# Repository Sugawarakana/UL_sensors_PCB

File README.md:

## Note: This project has been migrated into ULDSG

## Project Overview
Eagle-based PCB design for the UL project at the University of Michigan, Ann Arbor — Battery Control Group.

## Files
- `Connection.brd` — PCB layout file
- `Connection.sch` — Schematic file

## Tools
- Autodesk Eagle 9.6.2

## Descriptions
- **JP1 & JP2:** Female pin headers for Nucleo G431KB

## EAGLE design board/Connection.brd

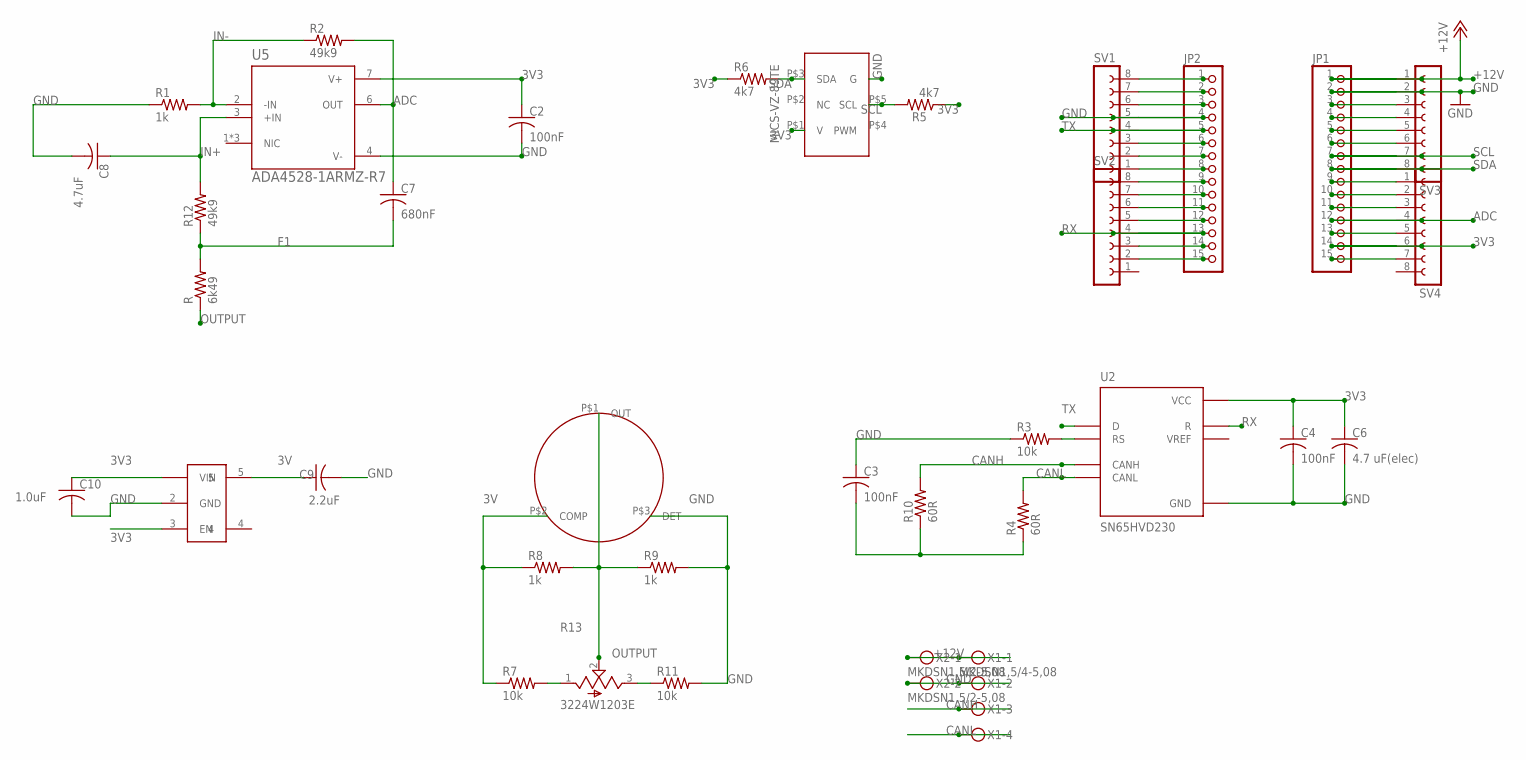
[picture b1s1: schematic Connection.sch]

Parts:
C2, C3, C4: 100nF; C0402
C6: 4.7 uF(elec); C0603
C7: 680nF; C1206
C8: 4.7uF; C1206
C9: 2.2uF; C0603
C10: 1.0uF; C0805
JP1, JP2: PINHD-1X15; 1X15
R: 6k49; R0603
R1, R8, R9: 1k; R0805
R2, R12: 49k9; R0603
R3, R7, R11: 10k; M1206
R4, R10: 60R; R0603
R5, R6: 4k7; M1206
R13: 3224W1203E; TRIM_3224W1203E
SV1, SV2, SV3, SV4: FE08-1; FE08
U2: SN65HVD230; SOIC127P599X175-8N
U5: ADA4528-1ARMZ-R7; SOP65P490X110-8N
U$1: MP7227; MP7227_FP
U$3: MIC5233
U$4: MICS-VZ-89TE; MICS-VZ-89TE_FP
X1: MKDSN1,5/4-5,08
X2: MKDSN1,5/2-5,08

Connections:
3V: C9.1, R7.1, R8.1, U$1.P$2 (COMP), U$3.5
3V3: C2.1, C4.1, C6.1, C10.1, JP1.14, R5.1, R6.1, SV4.6, U2.3 (VCC), U5.7 (V+), U$3.1 (VIN), U$3.3 (EN), U$4.P$1 (V); also elsewhere on the board
+12V: JP1.1, SV3.1, X1.1, X2.1; also elsewhere on the board
ADC: C7.1, JP1.12, R2.2, SV4.4, U5.6 (OUT); also elsewhere on the board
C1: C3.2, R4.1, R10.1
CANH: R10.2, U2.7 (CANH), X1.3
CANL: R4.2, U2.6 (CANL), X1.4
F1: C7.2, R.2, R12.1
GND: C2.2, C3.1, C4.2, C6.2, C8.2, C9.2, C10.2, JP1.2, JP2.4, R1.1, R3.1, R9.2, R11.2, SV1.5, SV3.2, U2.2 (GND), U5.4 (V-), U$1.P$3 (DET), U$3.2 (GND), U$4.P$6 (G), X1.2, X2.2; also elsewhere on the board
IN+: C8.1, R12.2, U5.3 (+IN)
IN-: R1.2, R2.1, U5.2 (-IN)
unnamed 12: JP1.6, SV3.6; also elsewhere on the board
unnamed 13: JP1.3, SV3.3; also elsewhere on the board
unnamed 14: JP1.4, SV3.4; also elsewhere on the board
unnamed 15: JP1.5, SV3.5; also elsewhere on the board
unnamed 16: JP1.9, SV4.1; also elsewhere on the board
unnamed 17: JP1.10, SV4.2; also elsewhere on the board
unnamed 18: JP1.11, SV4.3; also elsewhere on the board
unnamed 19: JP1.13, SV4.5; also elsewhere on the board
unnamed 20: JP1.15, SV4.7; also elsewhere on the board
unnamed 21: JP2.8, SV1.1; also elsewhere on the board
unnamed 22: JP2.7, SV1.2; also elsewhere on the board
unnamed 23: JP2.6, SV1.3; also elsewhere on the board
unnamed 24: JP2.3, SV1.6; also elsewhere on the board
unnamed 25: JP2.2, SV1.7; also elsewhere on the board
unnamed 26: JP2.1, SV1.8; also elsewhere on the board
unnamed 27: JP2.15, SV2.2; also elsewhere on the board
unnamed 28: JP2.14, SV2.3; also elsewhere on the board
unnamed 29: JP2.12, SV2.5; also elsewhere on the board
unnamed 30: JP2.11, SV2.6; also elsewhere on the board
unnamed 31: JP2.10, SV2.7; also elsewhere on the board
unnamed 32: JP2.9, SV2.8; also elsewhere on the board
OUTPUT: R.1, R8.2, R9.1, R13.2, U$1.P$1 (OUT)
PL: R7.2, R13.1
PR: R11.1, R13.3
RS: R3.2, U2.8 (RS)
RX: JP2.13, SV2.4, U2.4 (R); also elsewhere on the board
SCL: JP1.7, R5.2, SV3.7, U$4.P$5 (SCL); also elsewhere on the board
SDA: JP1.8, R6.2, SV3.8, U$4.P$3 (SDA); also elsewhere on the board
TX: JP2.5, SV1.4, U2.1 (D); also elsewhere on the board

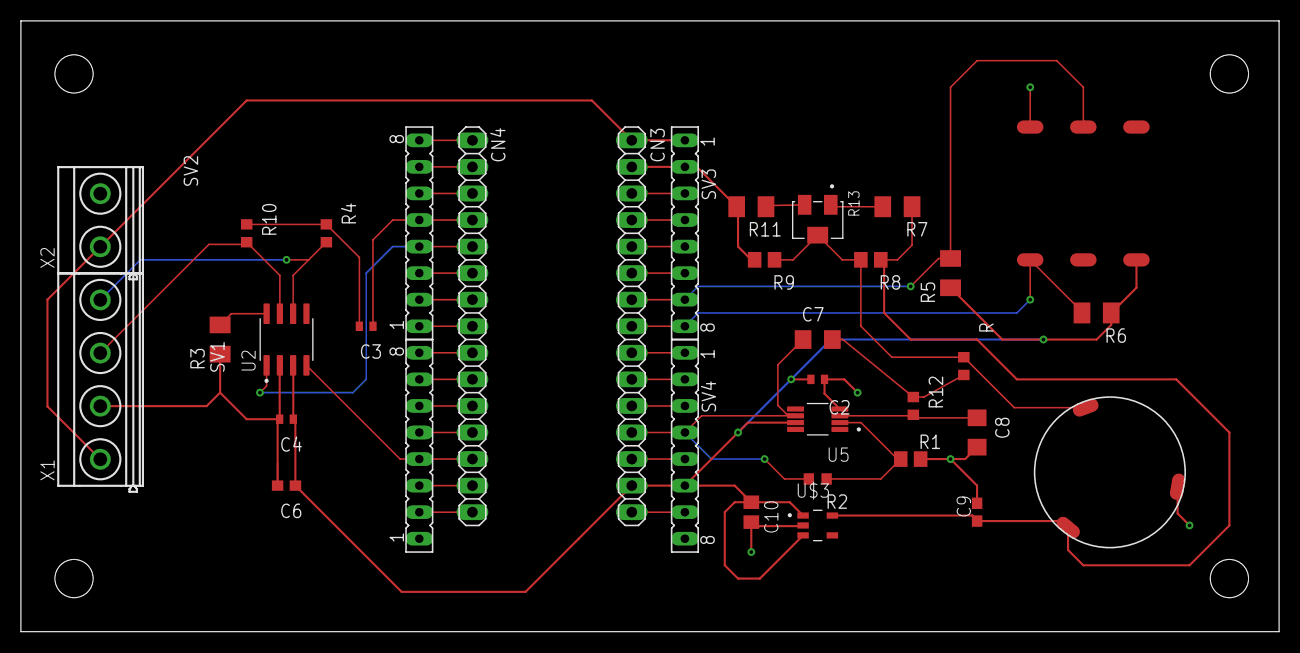
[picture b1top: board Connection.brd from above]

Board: 2 copper layers, 120.3 x 58.4 mm, 35 parts (0 on the bottom side), 40 nets.

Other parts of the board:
CN3: CN3; 1X15
CN4: CN4; 1X15

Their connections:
3V3: CN3.14; also elsewhere on the board
+12V: CN3.1; also elsewhere on the board
ADC: CN3.12; also elsewhere on the board
GND: CN3.2, CN4.4; also elsewhere on the board
unnamed 12: CN3.6; also elsewhere on the board
unnamed 13: CN3.3; also elsewhere on the board
unnamed 14: CN3.4; also elsewhere on the board
unnamed 15: CN3.5; also elsewhere on the board
unnamed 16: CN3.9; also elsewhere on the board
unnamed 17: CN3.10; also elsewhere on the board
unnamed 18: CN3.11; also elsewhere on the board
unnamed 19: CN3.13; also elsewhere on the board
unnamed 20: CN3.15; also elsewhere on the board
unnamed 21: CN4.8; also elsewhere on the board
unnamed 22: CN4.7; also elsewhere on the board
unnamed 23: CN4.6; also elsewhere on the board
unnamed 24: CN4.3; also elsewhere on the board
unnamed 25: CN4.2; also elsewhere on the board
unnamed 26: CN4.1; also elsewhere on the board
unnamed 27: CN4.15; also elsewhere on the board
unnamed 28: CN4.14; also elsewhere on the board
unnamed 29: CN4.12; also elsewhere on the board
unnamed 30: CN4.11; also elsewhere on the board
unnamed 31: CN4.10; also elsewhere on the board
unnamed 32: CN4.9; also elsewhere on the board
RX: CN4.13; also elsewhere on the board
SCL: CN3.7; also elsewhere on the board
SDA: CN3.8; also elsewhere on the board
TX: CN4.5; also elsewhere on the board

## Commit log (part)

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2026-04-22 Initial commit: Eagle PCB Connection board project
2026-04-22 Add ignore file
2026-04-22 Modify ignore
2026-04-22 Remove backup
2026-04-22 Add README
2026-04-23 move ch4 sensor away from nucleo female header pins for nucleo insertion move the 4pin CAN away from top of the nucleo space the other CAN pins to fit a terminal block
2026-04-23 Upload eagle lbr
2026-04-24 Used power terminal
2026-04-28 Optimized the size of PCB
2026-05-01 Modifications: 1. Flipped components to top layer 2. rearrange the spaces 3. Bolded pwr wires 4. Added copper 5. Sensor inlets toward edge 6. Terminals locked
2026-05-02 Polished the design
2026-06-02 Updated the design according to the real connection.
2026-06-03 Board & Schematic snapshot uploaded
